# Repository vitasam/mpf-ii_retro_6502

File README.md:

# MPF-II Micro-Professor 8-bit 6502 Retro Computer

**Microprofessor II** (**MPF II**), introduced in 1982, was Multitech's (later renamed [Acer](https://en.wikipedia.org/wiki/Acer_Inc.)) second branded computer product and also one of the [earliest](https://en.wikipedia.org/wiki/List_of_Apple_II_clones) [Apple II](https://en.wikipedia.org/wiki/Apple_II) clones. It does not look like most other computers.

## Technical information

- CPU: MOS Technology 6502
- Clock rate: 1 MHz
- RAM: 64 KB (including 16KB RAM mapped at the same address as the ROM)
- ROM: 16 KB (12 KB of which is a BASIC interpreter)
- Text modes: 40×24 (using graphics mode)
- Graphics modes: 280×192
- Colours: 8 colours
- Sound: 1 channel of 1-bit sound
- Connectors: Keyboard, Printer, Expansion port, cassette recorded input and output, Composite and TV-out
- Optional peripherals: 55 key full-size keyboard, Floppy disc drive, Thermal and Dot-matrix printers, Joystick
- Power supply: External PSU, 5,12V

## Differences to Apple II
([source](https://en.wikipedia.org/wiki/Microprofessor_II)).
- The MPF II was not totally compatible with the Apple II.
- The MPF II did not have Apple II's text mode. All the text was drawn on the screen by software rather than generated by hardware. It was the only cost-effective way to generate Chinese text on the screen at a time when a hardware-based Chinese character generator could cost hundreds of U.S. dollars.
- Like Apple II, MPF II had two graphics buffers. However, the second buffer was at address A000H while with Apple II it was at 4000H. The keyboard input was mapped to a different address than the Apple II making impossible to play Apple's games on the MPF II.
- MPF-II keyboard interface was very simple and consisted of an 8-bit output port and an input port that was directly connected to the keyboard matrix. The Apple joystick interface was not there, and instead, the joystick appeared as a keyboard with arrow keys and two other buttons.
- The external slot interface was also not compatible with the Apple II and could not use any standard interface cards including the Disk II controller.

# BASIC Binary Data Loader, a Proof Of Concept
An  [experiment](BasicDataLoader) for loading binary data into MPF-II memory by using STROBE and BUSY lines of a printer port and Arduino microcontroller as a server:

# Backlog

- [ ] Add MPF-II support to the [c2t](https://github.com/datajerk/c2t) utility. `c2t` is a command-line tool that can convert binary code/data and/or Apple-1/II Monitor text, as well as 140K disk images, into audio files suitable for use with the Apple-1 and II (II, II+, //e) cassette interface.

- [x] Modify the MIC output level to be compatible with the ZXTapeRecorderV2 input. See [details](Docs/Modifications/MIC_level).

- [ ] Add a volume control to the speaker (the speaker is very loud by default).

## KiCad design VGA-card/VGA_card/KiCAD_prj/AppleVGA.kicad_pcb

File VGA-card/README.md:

# Microprofessor-II VGA Card

This project introduces a custom VGA card for Microprofessor-II (MPF-II) computers, enabling high-quality RGB output to VGA monitors. It replaces the original composite video output with a crisp, clear digital signal, significantly enhancing the visual experience of MPF-II users.

*This VGA card is inspired by and based on the [Apple II VGA Card](https://github.com/markadev/AppleII-VGA) project, adapting its concepts to work with the MPF-II architecture.*

## MPF-II to Apple II Bus Adapter Board

### Overview

This adapter board provides a physical interface between the MPF-II (Micro-Professor II) and Apple II expansion ecosystems. It adapts the MPF-II peripheral bus connector to an Apple II-style bus connector, potentially allowing MPF-II users to connect certain Apple II expansion cards and peripherals.

Important Note: This adapter provides a simple electrical connection between the two bus systems. It does not perform full signal or timing conversion from MPF-II to Apple II standards. Compatibility with Apple II peripherals may be limited and may require additional modifications or custom software/firmware solutions.

### Key Features

1. Physical Adaptation: Transforms the MPF-II bus connector layout to match the Apple II bus connector layout.

2. Potential Compatibility: May enable the use of some Apple II expansion cards on the MPF-II system, subject to compatibility limitations.

3. Vertical Expansion: Unlike the original MPF-II's horizontal expansion, this adapter allows for vertical plugging of extension cards, including VGA cards. This can lead to a more compact and flexible system setup.

## Schematics

### Components
- Utilizes KiCAD components from [Apple-II](https://github.com/markadev/KiCad-AppleII) project

### Current Status
- [Rev.A](https://github.com/vitasam/mpf-ii_retro_6502/blob/main/VGA-card/MPF-II_bus_adapter/KiCAD_prj/mpf-ii-bus-adapter.pdf) of the PCB:

### Notes
- The schematic design is currently under development
- Updates will be made as progress continues

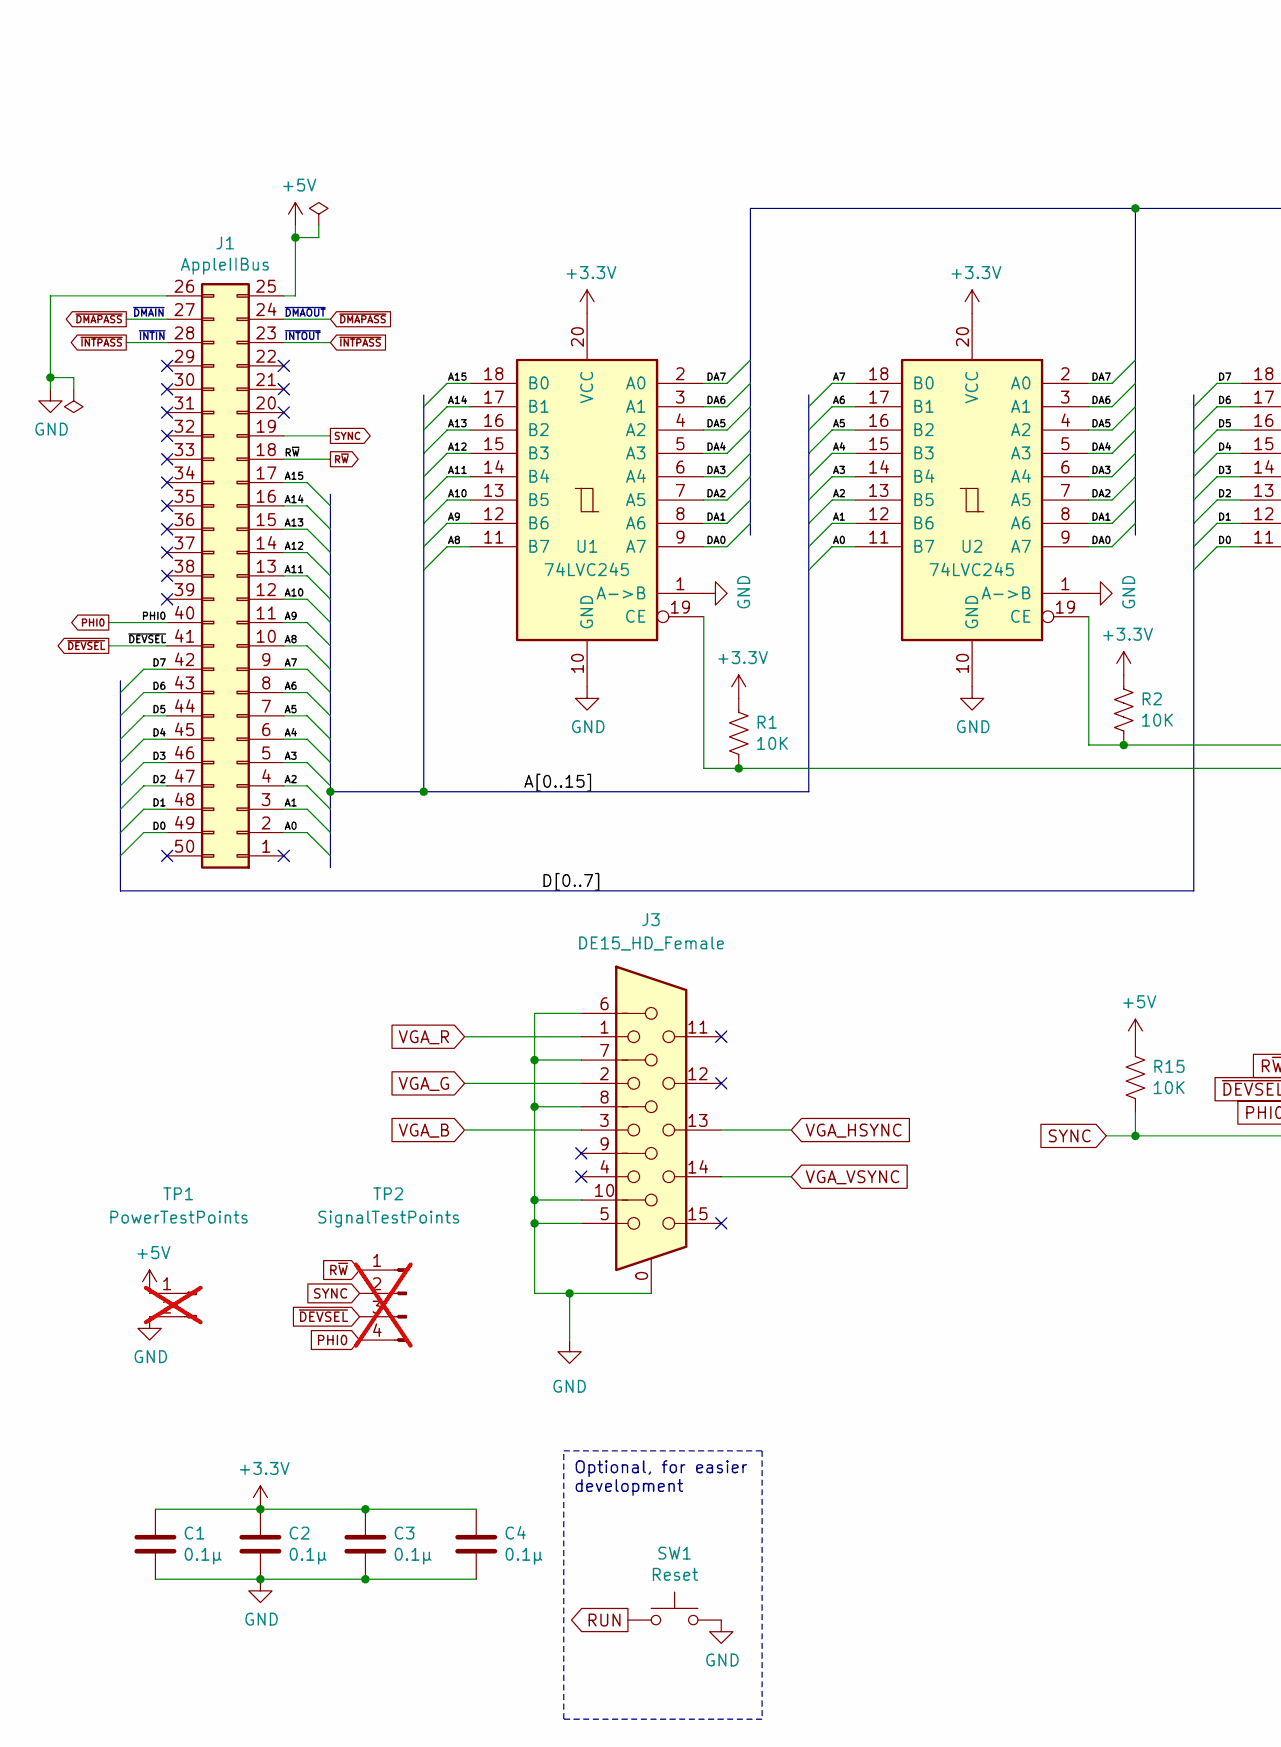
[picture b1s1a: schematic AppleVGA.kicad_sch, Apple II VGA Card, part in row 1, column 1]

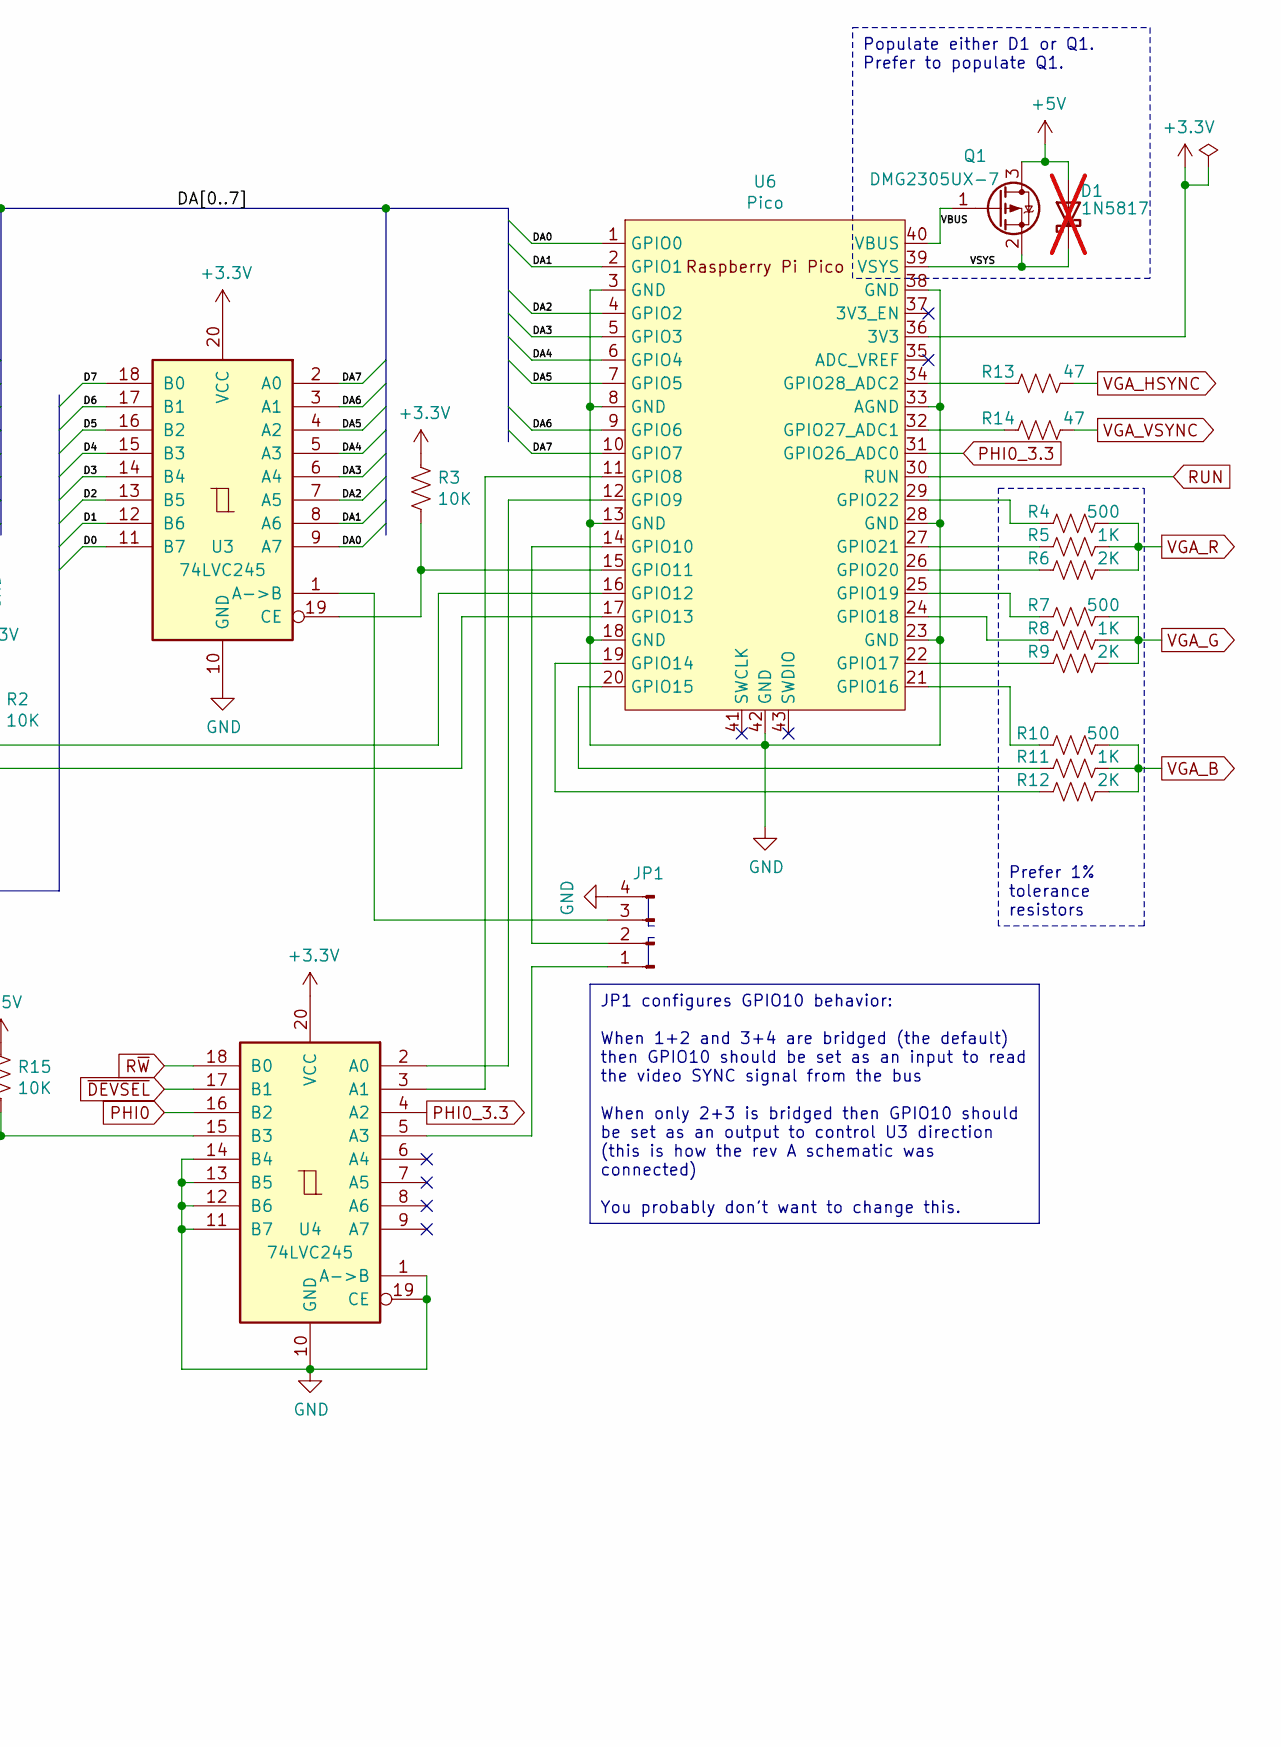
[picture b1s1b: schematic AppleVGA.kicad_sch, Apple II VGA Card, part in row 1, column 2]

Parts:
C1, C2, C3, C4: 0.1μ; C_Disc_D4.3mm_W1.9mm_P5.00mm; MouserNo 594-A104K15X7RF5TAA
D1: 1N5817; D_DO-41_SOD81_P10.16mm_Horizontal; MouserNo 511-1N5817; not fitted
J1: AppleIIBus; AppleIIBus_Edge
J3: DE15_HD_Female; DSUB-15-HD_Female_Horizontal_P2.29x1.98mm_EdgePinOffset8.35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
JP1: JumperPads; SolderJumper-4_P1.3mm_Bridged12_34_RoundedPad1.0x1.5mm_Numb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
Q1: DMG2305UX-7; SOT-23; MouserNo 621-DMG2305UX-7
R1, R2, R3, R15: 10K; R_Axial_DIN0207_L6.3mm_D2.5mm_P10.16mm_Thin_Horizontal; MouserNo 603-CFR-25JR-5210K
R4, R7, R10: 500; R_Axial_DIN0207_L6.3mm_D2.5mm_P10.16mm_Thin_Horizontal; MouserNo 603-MFR-25FBF52-499R
R5, R8, R11: 1K; R_Axial_DIN0207_L6.3mm_D2.5mm_P10.16mm_Thin_Horizontal; MouserNo 603-MFR-25FBF52-1K
R6, R9, R12: 2K; R_Axial_DIN0207_L6.3mm_D2.5mm_P10.16mm_Thin_Horizontal; MouserNo 603-MFR-25FBF52-2K
R13, R14: 47; R_Axial_DIN0207_L6.3mm_D2.5mm_P10.16mm_Thin_Horizontal; MouserNo 603-MFR-25FTF52-47R
SW1: Reset; SW_PUSH_6mm_H5mm; MouserNo 506-FSM4JH
TP1: PowerTestPoints; PinHeader_1x02_P2.54mm_Vertical; not fitted
TP2: SignalTestPoints; PinHeader_1x04_P2.54mm_Vertical; not fitted
U1, U2, U3, U4: 74LVC245; DIP-20_W7.62mm_Socket; MouserNo 595-SN74LVC245AN
U6: Pico; RPi_Pico_SMD_TH

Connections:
+3.3V: C1.1, C2.1, C3.1, C4.1, R1.1, R2.1, R3.1, U1.20 (VCC), U2.20 (VCC), U3.20 (VCC), U4.20 (VCC), U6.36 (3V3)
+5V: D1.2 (A), J1.25, Q1.3 (D), R15.1, TP1.1
/A0: J1.2, U2.11 (B7)
/A1: J1.3, U2.12 (B6)
/A2: J1.4, U2.13 (B5)
/A3: J1.5, U2.14 (B4)
/A4: J1.6, U2.15 (B3)
/A5: J1.7, U2.16 (B2)
/A6: J1.8, U2.17 (B1)
/A7: J1.9, U2.18 (B0)
/A8: J1.10, U1.11 (B7)
/A9: J1.11, U1.12 (B6)
/A10: J1.12, U1.13 (B5)
/A11: J1.13, U1.14 (B4)
/A12: J1.14, U1.15 (B3)
/A13: J1.15, U1.16 (B2)
/A14: J1.16, U1.17 (B1)
/A15: J1.17, U1.18 (B0)
/D0: J1.49, U3.11 (B7)
/D1: J1.48, U3.12 (B6)
/D2: J1.47, U3.13 (B5)
/D3: J1.46, U3.14 (B4)
/D4: J1.45, U3.15 (B3)
/D5: J1.44, U3.16 (B2)
/D6: J1.43, U3.17 (B1)
/D7: J1.42, U3.18 (B0)
/DA0: U1.9 (A7), U2.9 (A7), U3.9 (A7), U6.1 (GPIO0)
/DA1: U1.8 (A6), U2.8 (A6), U3.8 (A6), U6.2 (GPIO1)
/DA2: U1.7 (A5), U2.7 (A5), U3.7 (A5), U6.4 (GPIO2)
/DA3: U1.6 (A4), U2.6 (A4), U3.6 (A4), U6.5 (GPIO3)
/DA4: U1.5 (A3), U2.5 (A3), U3.5 (A3), U6.6 (GPIO4)
/DA5: U1.4 (A2), U2.4 (A2), U3.4 (A2), U6.7 (GPIO5)
/DA6: U1.3 (A1), U2.3 (A1), U3.3 (A1), U6.9 (GPIO6)
/DA7: U1.2 (A0), U2.2 (A0), U3.2 (A0), U6.10 (GPIO7)
/VBUS: Q1.1 (G), U6.40 (VBUS)
/VSYS: D1.1 (K), Q1.2 (S), U6.39 (VSYS)
GND: C1.2, C2.2, C3.2, C4.2, J1.26, J3.0, J3.5, J3.6, J3.7, J3.8, J3.10, JP1.4, SW1.2, TP1.2, U1.1 (A->B), U1.10 (GND), U2.1 (A->B), U2.10 (GND), U3.10 (GND), U4.1 (A->B), U4.10 (GND), U4.11 (B7), U4.12 (B6), U4.13 (B5), U4.14 (B4), U4.19 (CE), U6.3 (GND), U6.8 (GND), U6.13 (GND), U6.18 (GND), U6.23 (GND), U6.28 (GND), U6.33 (AGND), U6.38 (GND), U6.42 (GND)
unnamed: JP1.1, U4.5 (A3)
unnamed: JP1.2, U6.14 (GPIO10)
unnamed: JP1.3, U3.1 (A->B)
unnamed: R1.2, U1.19 (CE), U6.17 (GPIO13)
unnamed: R2.2, U2.19 (CE), U6.16 (GPIO12)
unnamed: R3.2, U3.19 (CE), U6.15 (GPIO11)
unnamed: U4.2 (A0), U6.12 (GPIO9)
unnamed: U4.3 (A1), U6.11 (GPIO8)
unnamed: R12.1, U6.19 (GPIO14)
unnamed: R11.1, U6.20 (GPIO15)
unnamed: R10.1, U6.21 (GPIO16)
unnamed: R9.1, U6.22 (GPIO17)
unnamed: R8.1, U6.24 (GPIO18)
unnamed: R7.1, U6.25 (GPIO19)
unnamed: R6.1, U6.26 (GPIO20)
unnamed: R5.1, U6.27 (GPIO21)
unnamed: R4.1, U6.29 (GPIO22)
unnamed: R14.1, U6.32 (GPIO27_ADC1)
unnamed: R13.1, U6.34 (GPIO28_ADC2)
PHI0: J1.40, TP2.4, U4.16 (B2)
PHI0_3.3: U4.4 (A2), U6.31 (GPIO26_ADC0)
RUN: SW1.1, U6.30 (RUN)
R~W: J1.18, TP2.1, U4.18 (B0)
SYNC: J1.19, R15.2, TP2.2, U4.15 (B3)
VGA_B: J3.3, R10.2, R11.2, R12.2
VGA_G: J3.2, R7.2, R8.2, R9.2
VGA_HSYNC: J3.13, R13.2
VGA_R: J3.1, R4.2, R5.2, R6.2
VGA_VSYNC: J3.14, R14.2
~DEVSEL: J1.41, TP2.3, U4.17 (B1)
~DMAPASS: J1.24, J1.27
~INTPASS: J1.23, J1.28

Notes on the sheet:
Optional, for easier development
Populate either D1 or Q1. Prefer to populate Q1.
JP1 configures GPIO10 behavior: When 1+2 and 3+4 are bridged (the default) then GPIO10 should be set as an input to read the video SYNC signal from the bus When only 2+3 is bridged then GPIO10 should be set as an output to control U3 direction (this is how the rev A schematic was connected) You pro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
Prefer 1% tolerance resistors
~{DMAIN}
~{INTOUT}
~{DMAOUT}
~{INTIN}

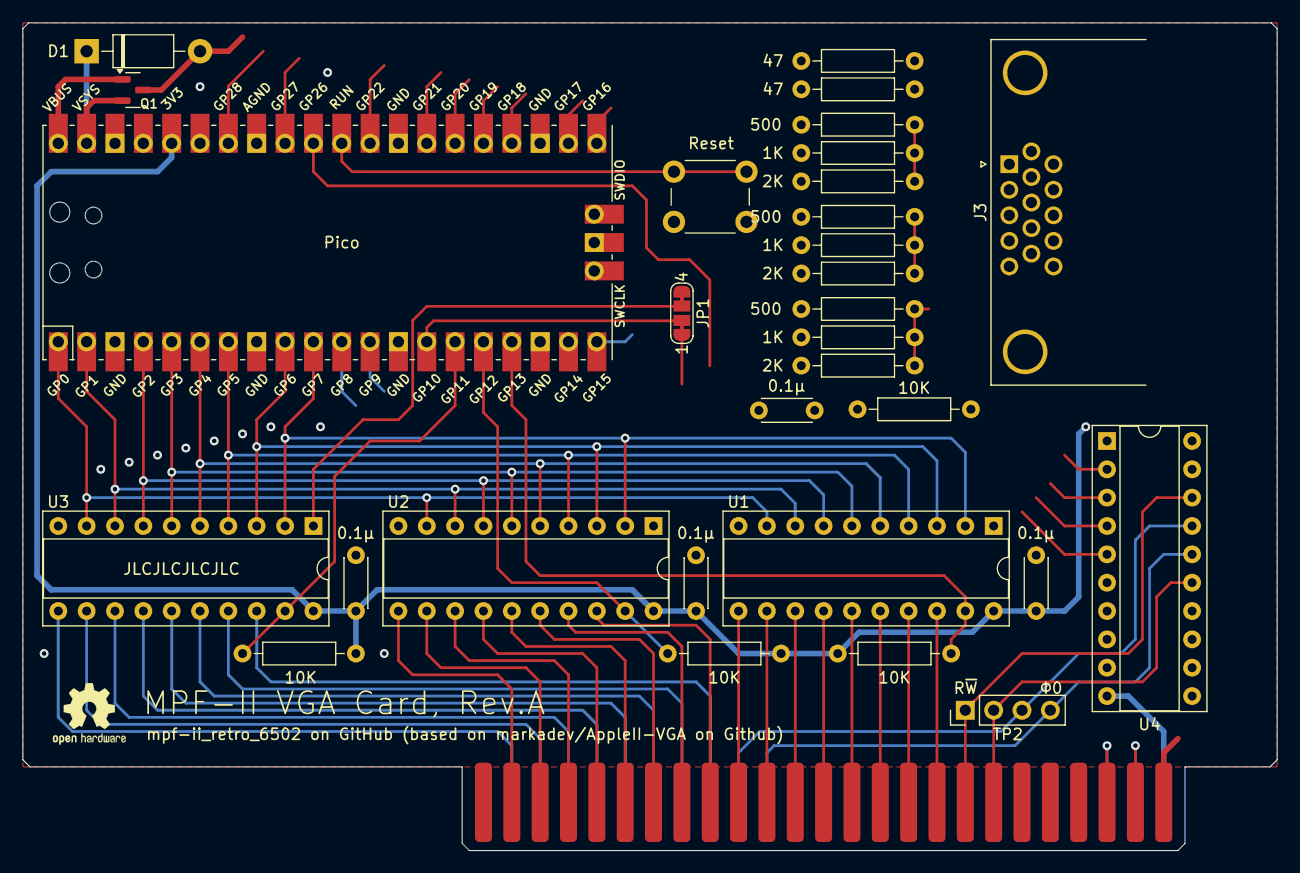
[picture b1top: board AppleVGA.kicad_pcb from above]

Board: 2 copper layers, 112.4 x 74.2 mm, 31 parts (0 on the bottom side), 69 nets.

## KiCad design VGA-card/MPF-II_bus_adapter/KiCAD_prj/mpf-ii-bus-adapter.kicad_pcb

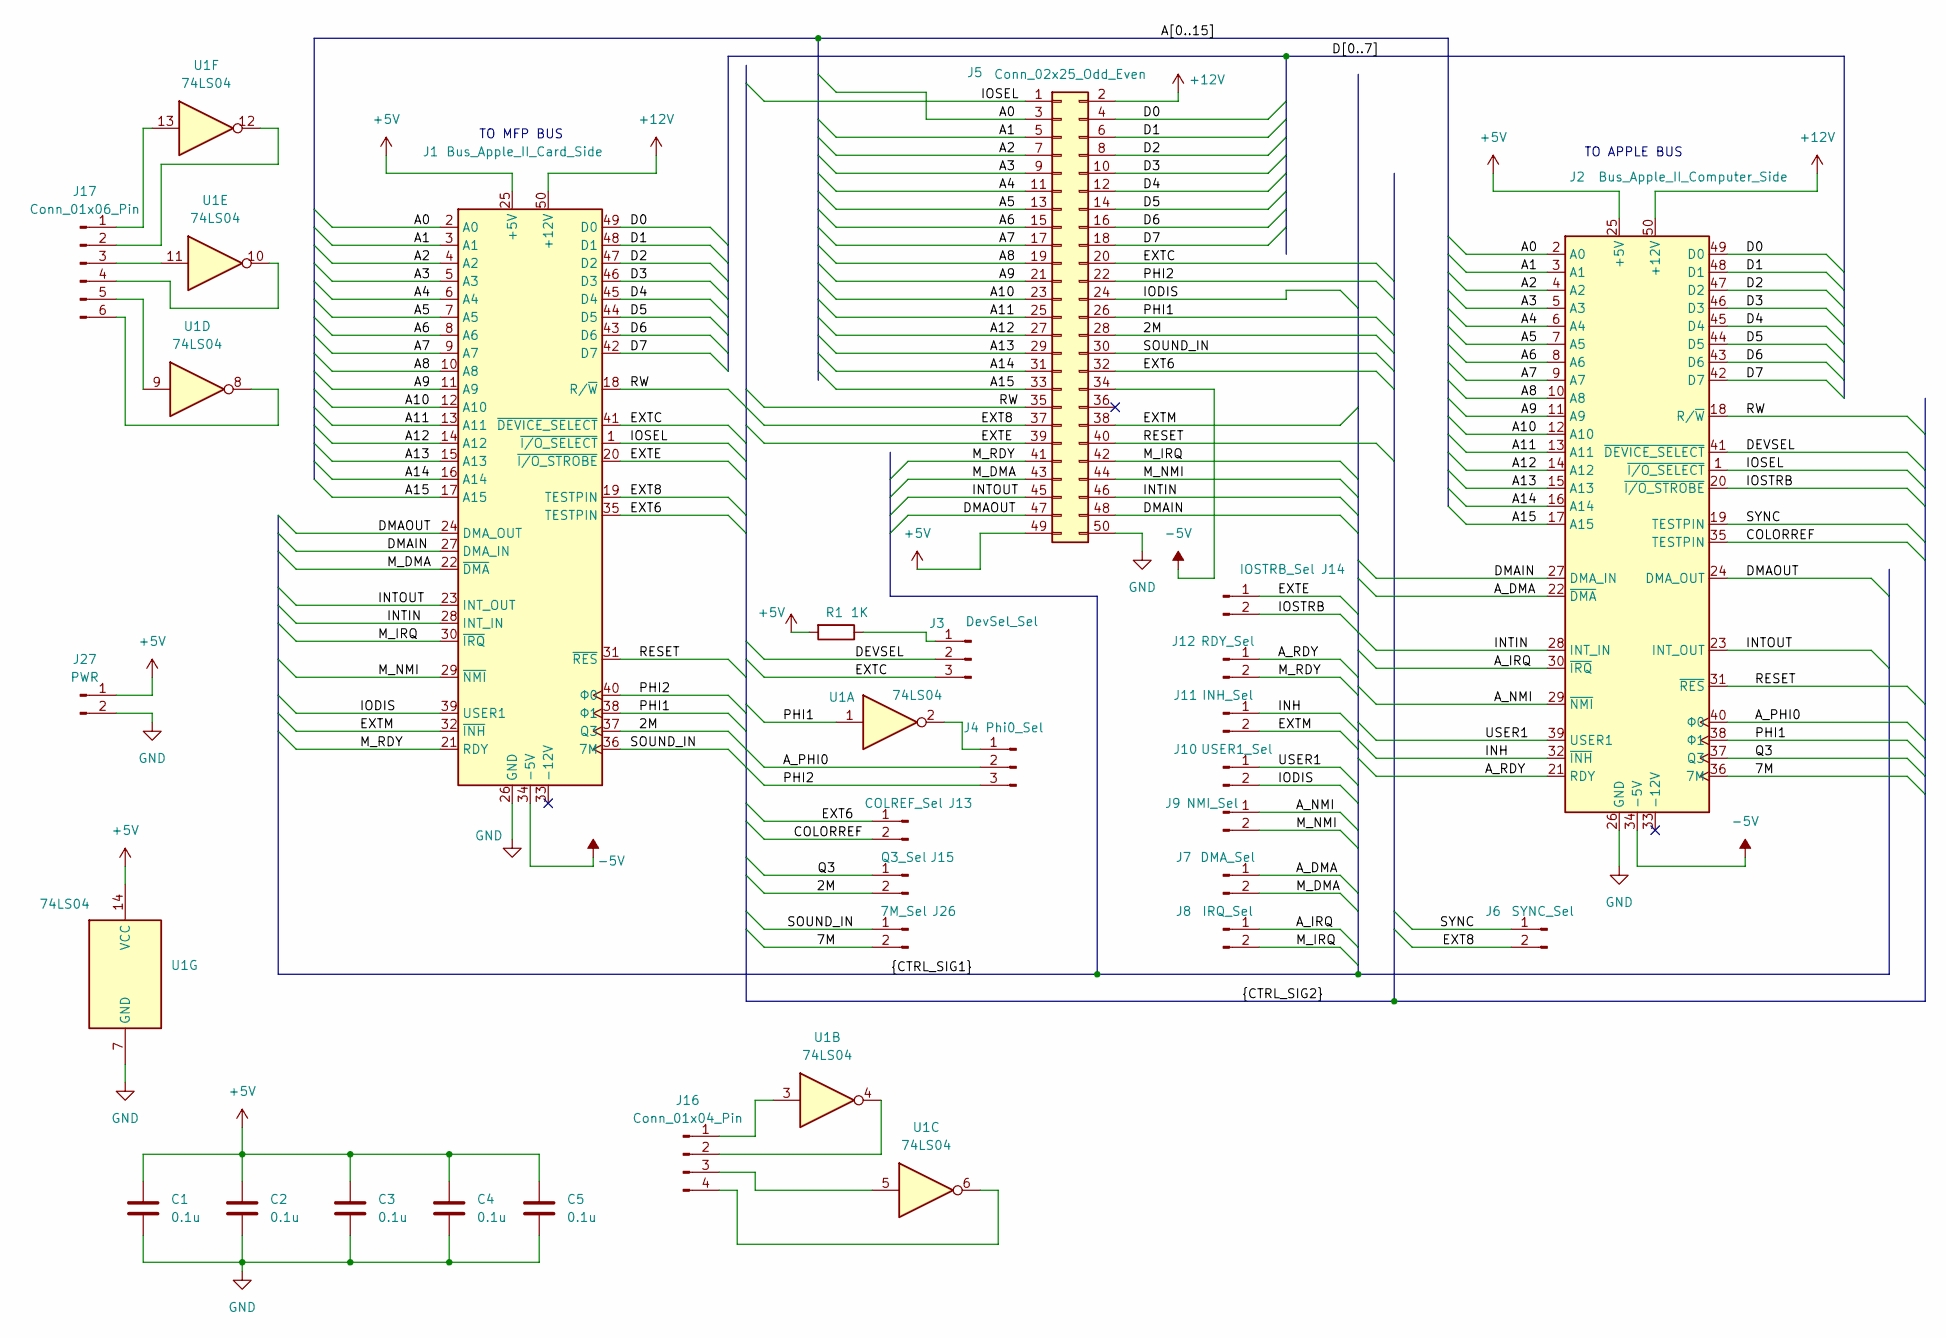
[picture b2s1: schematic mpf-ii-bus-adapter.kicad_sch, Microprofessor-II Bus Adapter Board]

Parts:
C1, C2, C3, C4, C5: 0.1u; C_Disc_D4.3mm_W1.9mm_P5.00mm
J1: Bus_Apple_II_Card_Side; Peripheral_MPFII_Bus_Edge
J2: Bus_Apple_II_Computer_Side; EDAC_395-050-520-201_CounterClockwise
J3: DevSel_Sel; PinHeader_1x03_P2.54mm_Vertical
J4: Phi0_Sel; PinHeader_1x03_P2.54mm_Vertical
J5: Conn_02x25_Odd_Even; PinHeader_2x25_P2.54mm_Vertical
J6: SYNC_Sel; PinHeader_1x02_P2.54mm_Vertical
J7: DMA_Sel; PinHeader_1x02_P2.54mm_Vertical
J8: IRQ_Sel; PinHeader_1x02_P2.54mm_Vertical
J9: NMI_Sel; PinHeader_1x02_P2.54mm_Vertical
J10: USER1_Sel; PinHeader_1x02_P2.54mm_Vertical
J11: INH_Sel; PinHeader_1x02_P2.54mm_Vertical
J12: RDY_Sel; PinHeader_1x02_P2.54mm_Vertical
J13: COLREF_Sel; PinHeader_1x02_P2.54mm_Vertical
J14: IOSTRB_Sel; PinHeader_1x02_P2.54mm_Vertical
J15: Q3_Sel; PinHeader_1x02_P2.54mm_Vertical
J16: Conn_01x04_Pin; PinHeader_1x04_P2.54mm_Vertical
J17: Conn_01x06_Pin; PinHeader_1x06_P2.54mm_Vertical
J26: 7M_Sel; PinHeader_1x02_P2.54mm_Vertical
J27: PWR; PinHeader_1x02_P2.54mm_Vertical
R1: 1K; R_Axial_DIN0207_L6.3mm_D2.5mm_P10.16mm_Horizontal
U1: 74LS04; DIP-14_W7.62mm

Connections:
+5V: C1.1, C2.1, C3.1, C4.1, C5.1, J1.25 (+5V), J2.25 (+5V), J5.49, J27.1, R1.2, U1.14 (VCC)
+12V: J1.50 (+12V), J2.50 (+12V), J5.2
-5V: J1.34 (-5V), J2.34 (-5V), J5.34
/2M: J1.37 (Q3), J5.28, J15.2
/7M: J2.36 (7M), J26.2
/A0: J1.2 (A0), J2.2 (A0), J5.3
/A1: J1.3 (A1), J2.3 (A1), J5.5
/A2: J1.4 (A2), J2.4 (A2), J5.7
/A3: J1.5 (A3), J2.5 (A3), J5.9
/A4: J1.6 (A4), J2.6 (A4), J5.11
/A5: J1.7 (A5), J2.7 (A5), J5.13
/A6: J1.8 (A6), J2.8 (A6), J5.15
/A7: J1.9 (A7), J2.9 (A7), J5.17
/A8: J1.10 (A8), J2.10 (A8), J5.19
/A9: J1.11 (A9), J2.11 (A9), J5.21
/A10: J1.12 (A10), J2.12 (A10), J5.23
/A11: J1.13 (A11), J2.13 (A11), J5.25
/A12: J1.14 (A12), J2.14 (A12), J5.27
/A13: J1.15 (A13), J2.15 (A13), J5.29
/A14: J1.16 (A14), J2.16 (A14), J5.31
/A15: J1.17 (A15), J2.17 (A15), J5.33
/A_DMA: J2.22 (~DMA), J7.1
/A_IRQ: J2.30 (~IRQ), J8.1
/A_NMI: J2.29 (~NMI), J9.1
/A_PHI0: J2.40 (Φ0), J4.2
/A_RDY: J2.21 (RDY), J12.1
/COLORREF: J2.35 (TESTPIN), J13.2
/D0: J1.49 (D0), J2.49 (D0), J5.4
/D1: J1.48 (D1), J2.48 (D1), J5.6
/D2: J1.47 (D2), J2.47 (D2), J5.8
/D3: J1.46 (D3), J2.46 (D3), J5.10
/D4: J1.45 (D4), J2.45 (D4), J5.12
/D5: J1.44 (D5), J2.44 (D5), J5.14
/D6: J1.43 (D6), J2.43 (D6), J5.16
/D7: J1.42 (D7), J2.42 (D7), J5.18
/DEVSEL: J2.41 (~DEVICE_SELECT), J3.2
/DMAIN: J1.27 (DMA_IN), J2.27 (DMA_IN), J5.48
/DMAOUT: J1.24 (DMA_OUT), J2.24 (DMA_OUT), J5.47
/EXT6: J1.35 (TESTPIN), J5.32, J13.1
/EXT8: J1.19 (TESTPIN), J5.37, J6.2
/EXTC: J1.41 (~DEVICE_SELECT), J3.3, J5.20
/EXTE: J1.20 (~I/O_STROBE), J5.39, J14.1
/EXTM: J1.32 (~INH), J5.38, J11.2
/INH: J2.32 (~INH), J11.1
/INTIN: J1.28 (INT_IN), J2.28 (INT_IN), J5.46
/INTOUT: J1.23 (INT_OUT), J2.23 (INT_OUT), J5.45
/IODIS: J1.39 (USER1), J5.24, J10.2
/IOSEL: J1.1 (~I/O_SELECT), J2.1 (~I/O_SELECT), J5.1
/IOSTRB: J2.20 (~I/O_STROBE), J14.2
/M_DMA: J1.22 (~DMA), J5.43, J7.2
/M_IRQ: J1.30 (~IRQ), J5.42, J8.2
/M_NMI: J1.29 (~NMI), J5.44, J9.2
/M_RDY: J1.21 (RDY), J5.41, J12.2
/PHI1: J1.38 (Φ1), J2.38 (Φ1), J5.26, U1.1
/PHI2: J1.40 (Φ0), J4.3, J5.22
/Q3: J2.37 (Q3), J15.1
/RESET: J1.31 (~RES), J2.31 (~RES), J5.40
/RW: J1.18 (R/~W), J2.18 (R/~W), J5.35
/SOUND_IN: J1.36 (7M), J5.30, J26.1
/SYNC: J2.19 (TESTPIN), J6.1
/USER1: J2.39 (USER1), J10.1
GND: C1.2, C2.2, C3.2, C4.2, C5.2, J1.26 (GND), J2.26 (GND), J5.50, J27.2, U1.7 (GND)
unnamed: J3.1, R1.1
unnamed: J4.1, U1.2
unnamed: J16.1, U1.3
unnamed: J16.2, U1.4
unnamed: J16.3, U1.5
unnamed: J16.4, U1.6
unnamed: J17.1, U1.13
unnamed: J17.2, U1.12
unnamed: J17.3, U1.11
unnamed: J17.4, U1.10
unnamed: J17.5, U1.9
unnamed: J17.6, U1.8

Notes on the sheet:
TO APPLE BUS
TO MFP BUS

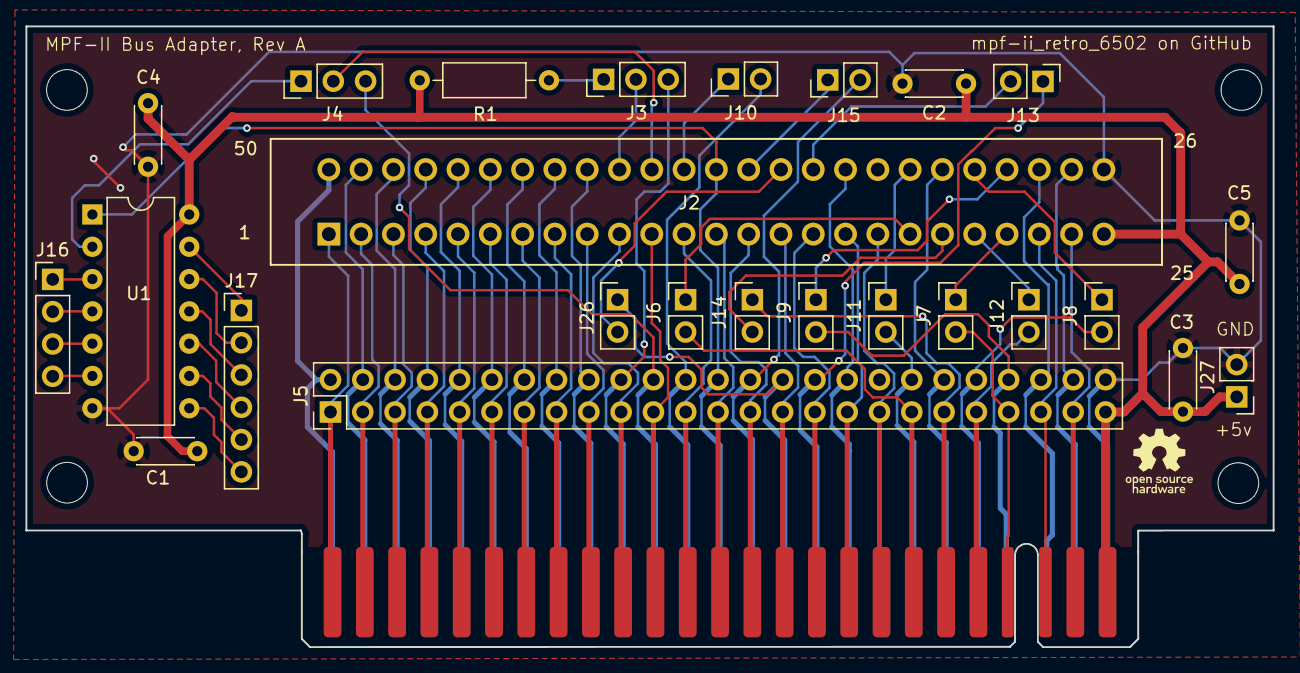
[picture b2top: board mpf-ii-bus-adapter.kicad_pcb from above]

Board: 2 copper layers, 98.1 x 48.8 mm, 26 parts (0 on the bottom side), 74 nets.

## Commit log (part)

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2022-09-01 README updated
2022-09-01 Syntax updated
2022-09-07 KiCAD project added
2022-09-07 KiCAD schematics updated
2022-09-07 KiCAD ERC errors have been fixed
2022-09-10 Asm listing updated
2022-09-10 Links updated
2022-09-13 KiCAD error fixes
2022-09-14 KiCAD project renamed
2022-09-14 KiCAD connections sheet modified
2022-09-14 KiCAD connections sheet renamed
2022-09-14 Old connection file deleted
2022-09-14 KiCAD project README updated
2022-09-14 Schematics files updated
2023-06-25 MPF-II display DOC added
2024-04-03 README fix
2024-07-16 KiCAD project updated from AppleII-VGA
2024-07-17 Bus pinouts added
2024-07-17 Pinouts PDF updated
2024-07-19 VGA card readme updated
2024-07-19 mpf-II KiCAD project added
2024-07-19 [Bus-adapter] Address bus added to schematics
2024-07-19 Data bus added
2024-07-19 DEVSEL and RW are added
2024-07-19 Clock signals added
2024-07-19 Schematics updated
2024-07-20 Schematic PDF added
2024-07-21 Bus refactoring
2024-07-21 ERC fix for the schematics
2024-07-21 Schematics PDF updated
2024-07-21 MPF-II bus docs updated
2024-07-21 Adapter PCB started
2024-07-22 Schematics and PCB updated
2024-07-23 PCB updated
2024-07-23 PCB silk updated
2024-07-23 PCB edge cut updated
2024-07-24 PCB is ready
2024-07-24 Filled zones added
2024-07-26 Docs updated
2024-07-26 Schematics updated with bus pinheader connector
2024-07-26 New PCB started
2024-07-26 Schematics connections list updated
2024-07-28 PCB connector updated
2024-07-29 Bus pin-header connector PCB
2024-07-31 PCB layout finished, ready for testing
2024-07-31 DRC status OK
2024-07-31 PCB rev. A is ready
2024-08-01 PCB updated, PDF exported
2024-08-02 Bus adapter picture updated
2024-08-09 Gerber files generated
2024-08-11 VGA card KiCAD project added
2024-08-11 VGA card KiCAD project updated
2024-08-13 VGA card KiCAD updated
2024-08-15 Readme uypdated
2024-08-17 VGA card KiCAD project deleted
2024-08-17 MPF-II VGA card KiCAD project added
2024-08-17 Sch.updated
2024-08-18 VGA card schematics updated
2024-08-18 Description updated
2024-08-19 Sch updated
2024-09-10 Gitignore added
2024-09-10 Card schematics updated
2024-09-11 Obsolete files removed
2024-09-11 PCB PDF added

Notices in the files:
VGA-card/KiCAD/AppleVGA.kicad_sch:
Licensed under CERN-OHL-P V2.0 (https://ohwr.org/cern_ohl_p_v2.txt)
Copyright (c) 2021-2023 Mark Aikens
VGA-card/MPF-II_bus_adapter/KiCAD_prj/mpf-ii-bus-adapter.kicad_pcb:
Copyright (c) 2024 The Random DIY
